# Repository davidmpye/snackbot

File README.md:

**Snackbot** is Makerspace's vending machine. It started life as a Polyvend
machine with a dead original controller (or at least it died while being experimented with...)
it's now a hybrid of a Raspberry Pi (running the user interface) and two RP2040 Pi Pico boards (driving the
hardware), all written in Rust.

This repository contains everything needed to reproduce the conversion:
firmware, PCB designs, the Pi-side application, and the 3D-printed / laser-cut
fixings.

Of note, it supports an MDB credit card reader, allowing contactless card payments

> 📷 *Photos to follow.*

---

## Architecture

```
                 ┌──────────────────────────────────────────┐
                 │ Raspberry Pi + Hyperpixel 480x800 display │
                 │          vmc-host (GTK4 app)              │
                 └───────────┬──────────────────┬───────────┘
                     USB HID │ + postcard-rpc   │ USB postcard-rpc
                             │                  │
            ┌────────────────┴───┐      ┌───────┴────────────────────────┐
            │  matrix-keyboard   │      │       vmc (RP2040 + PCB)        │
            │  (RP2040 + PCB)    │      │                                 │
            │                    │      │  • dispenser motor matrix       │
            │  • 3x8 keypad →    │      │  • MDB bus: coin acceptor &     │
            │    USB keyboard    │      │    cashless (card) reader       │
            │  • optional I2C    │      │  • chiller control + thermistor │
            │    text LCD        │      │  • hardware watchdog            │
            └────────────────────┘      └─────────────────────────────────┘
```

1. The customer types a selection on the machine's original membrane keypad
   (e.g. `A` then `4`). The **matrix-keyboard** Pico presents this to the Pi as
   an ordinary USB keyboard.
2. **vmc-host** shows the item, picture and price on the display and asks for
   confirmation (✔ / ✖).
3. On confirmation the host sends a `Vend` command to the **vmc** Pico, which
   collects payment over MDB (coins or contactless), drives the appropriate
   spiral/can motor, checks for a successful drop, and reports back.
4. The host shows success/failure and returns to idle.

The two Picos talk to the Pi using [postcard-rpc](https://github.com/jamesmunns/postcard-rpc)
over USB. The wire protocols are defined in small shared `*-icd` crates so the
host and firmware can never disagree about message formats.

---

## Repository layout

| Path | What it is |
|------|------------|
| [`vmc/fw`](vmc/fw) | **Vending Machine Controller firmware** – `no_std` Rust on RP2040 using [Embassy](https://embassy.dev). Drives motors, MDB peripherals, chiller and watchdog; exposes a postcard-rpc server over USB. |
| [`vmc/vmc-icd`](vmc/vmc-icd) | Interface Control Document crate for the VMC – shared request/response types and endpoint definitions. |
| [`vmc/pcb`](vmc/pcb) | KiCad project for the VMC board (power, level shifters, MDB interface, motor driver). Gerber job file included. |
| [`matrix-keyboard/fw`](matrix-keyboard/fw) | Firmware for the keypad board – USB HID keyboard + postcard-rpc endpoints for an optional I2C LCD. |
| [`matrix-keyboard/keyboard-icd`](matrix-keyboard/keyboard-icd) | ICD crate for the keypad board. |
| [`matrix-keyboard/pcb`](matrix-keyboard/pcb) | KiCad project for the keypad interface board (includes 3V3→5V level shifting for 5V LCDs). |
| [`vmc-host`](vmc-host) | The GTK4 application that runs on the Raspberry Pi – UI, state machine, stock list, and USB clients for both Picos. |
| [`fixings`](fixings) | OpenSCAD sources for the display mount, retaining tabs, LCD frame and laser-cut acrylic windows. See [`fixings/README.md`](fixings/README.md). |

---

## Components in detail

### `vmc` – Vending Machine Controller

The VMC firmware runs a set of Embassy tasks:

- **Motor driver** – drives the dispenser motor matrix via an 8-bit data bus
  plus three clock lines, OE and CLR (GPIO 0–12). Detects home position,
  stuck motors, and "one or no cans left" on the can vendor.
- **MDB (Multi-Drop Bus)** – the 9-bit serial bus used by vending peripherals,
  implemented with a PIO-backed 9-bit UART on GPIO 20/21. Two poll tasks handle
  the **coin acceptor** and a **cashless (card) device**.
- **Chiller** – reads a thermistor on ADC0 (GPIO 26) and publishes
  `ChillerStatus` to the host.
- **Watchdog** – hardware watchdog with a heartbeat LED on GPIO 22.
- **USB** – enumerates as a composite device, manufacturer `Snackbot`,
  product `vmc` (VID `0xDEAD`, PID `0xBEEF`).

The postcard-rpc API (from `vmc-icd`):

| Endpoint | Request | Response | Purpose |
|----------|---------|----------|---------|
| `/vmc/itemavailable` | `VendCommand` | `VendResult` | Check an item can be vended |
| `/vmc/vend` | `VendCommand` | `VendResult` | Take payment, then dispense |
| `/vmc/forcedispense` | `VendCommand` | `VendResult` | Dispense **without charging** (maintenance) |
| `/vmc/cancelvend` | `()` | `VendResult` | Cancel an in-progress vend *(not yet implemented)* |
| `/vmc/collectpayment` | `VendCommand` | `VendResult` | Charge without dispensing – lets people pay for e.g. filament |

| Topic (device → host) | Payload |
|-----------------------|---------|
| `/vmc/vend_progress` | `AwaitingPayment` / `Dispensing` |
| `/vmc/status/chiller` | `ChillerStatus` |

`VendCommand` is `{ row: u8, col: u8, price: u16 }` with the price in unscaled
pence. Failures are reported as a `VendError` (`MotorNotPresent`,
`MotorNotHome`, `MotorStuckHome`, `MotorStuckNotHome`, `OneOrNoCansLeft`,
`NoDropDetected`, `InvalidAddress`, `Cancelled`, `PaymentFailed`, `CommsFault`).

### `matrix-keyboard` – keypad interface

A small PCB that plugs into the vending machine's original 3×8 matrix keypad
header. The firmware scans the matrix and appears to the Pi as a **USB HID
keyboard**, so no custom input driver is needed on the Pi side.

It also exposes postcard-rpc endpoints for an optional **I2C character LCD**
(useful as a cheap secondary display, or as the *only* display if you don't
fit the Hyperpixel):

| Endpoint | Request | Purpose |
|----------|---------|---------|
| `setText` | `[[u8; 32]; 2]` | Set two 32-character lines of text |
| `setBacklight` | `bool` | Backlight on/off |

Topic `serviceMode` (`bool`) is published to the host.

### `vmc-host` – the Pi application

A GTK4 app (`uk.org.makerspace.snackbot`) sized for a 480×800 portrait display
(Pimoroni Hyperpixel 4). It is a simple event-driven state machine:

```
Idle ─▶ AwaitingConfirmation ─▶ AwaitingPayment ─▶ Dispensing ─▶ VendSuccess
  ▲            │                      │                 │              │
  │            ✖ cancel               ✖ cancel          └──▶ VendFailed │
  └────────────┴──────────────────────┴───────────── timeout / 2s ─────┘
```

- Letters `A`–`H` select a row, digits `0`–`9` a column; `Return` is ✔ confirm,
  `Escape` is ✖ cancel.
- Returns to idle automatically after 30 s of inactivity.
- Each screen is a GTK widget in a `Stack` (`make_selection_box`,
  `confirm_item_box`, `make_payment_box`, `vend_in_progress_box`, etc.).
- The stock list (name, image, price, row/col) currently lives in
  [`vmc-host/src/stock_info.rs`](vmc-host/src/stock_info.rs); product images
  are in `vmc-host/src/images/`.
- `rpc_shim.rs` spawns a Tokio runtime hosting the postcard-rpc clients for the
  VMC and the LCD, bridged to the GLib main loop with `async-channel`.

### `fixings` – mechanical parts

OpenSCAD sources for:

- `hyperpixel_mount.scad` / `hyperpixel_retaining_tabs.scad` – 3D-printed
  bracket and tabs to hold the Pi + Hyperpixel behind the fascia.
- `hyperpixel_lcd_window.scad` – laser-cut 3 mm clear acrylic window.
- `i2c_lcd_frame.scad` / `i2c_lcd_window.scad` – frame and window for the
  optional I2C text display.

---

## Building

### Prerequisites

- Rust toolchain (the firmware crates pin their version via
  `rust-toolchain.toml`; `rustup` will pick it up automatically).
- For firmware: the `thumbv6m-none-eabi` target and
  [`probe-rs`](https://probe.rs) (or `elf2uf2-rs` if you'd rather flash over
  USB bootloader).
- For the host: GTK4 development libraries (`libgtk-4-dev` on
  Debian/Raspberry Pi OS) and `libudev`.

### Firmware (either Pico)

```bash
cd vmc/fw            # or matrix-keyboard/fw
cargo run --release  # flashes via probe-rs (see .cargo/config.toml)
```

To produce a UF2 instead, swap the runner in `.cargo/config.toml` for the
commented-out `elf2uf2-rs -d` line, hold BOOTSEL while plugging in the Pico,
and `cargo run --release` again.

Logging is via `defmt` over RTT; set `DEFMT_LOG=debug` for more chatter.

The VMC firmware depends on two companion crates by the same author:
[`mdb-async`](https://github.com/davidmpye/mdb-async) and
[`pio-9bit-uart-async`](https://github.com/davidmpye/pio-9bit-uart-async).

### Host application

```bash
cd vmc-host
cargo build --release
./target/release/vmc-host
```

The app opens USB devices by product string (`vmc` and `matrix-keyboard`), so
you'll want a udev rule granting your user access to them, e.g.:

```
# /etc/udev/rules.d/99-snackbot.rules
SUBSYSTEM=="usb", ATTR{idVendor}=="dead", ATTR{idProduct}=="beef", MODE="0666"
```

(adjust for the keyboard board's VID/PID as well), then
`sudo udevadm control --reload && sudo udevadm trigger`.

For a kiosk deployment, run it under a minimal Wayland/X session on boot with
the Hyperpixel in portrait orientation.

### Hardware

Open the `.kicad_pro` files in `vmc/pcb` and `matrix-keyboard/pcb` with
KiCad 8+. Render the `.scad` files in `fixings/` with OpenSCAD and export STL
(for printing) or DXF (for laser cutting).

---

## Status / TODO

- [ ] `CancelVend` endpoint on the VMC
- [ ] Move stock list out of `stock_info.rs` into a config file
- [ ] Hook up `ItemAvailable` / `CollectPaymentOnly` in the host UI
- [ ] Photos and wiring diagrams
- [ ] Chiller status display on the host

---

## License

GPL-3.0 – see [LICENSE](LICENSE).

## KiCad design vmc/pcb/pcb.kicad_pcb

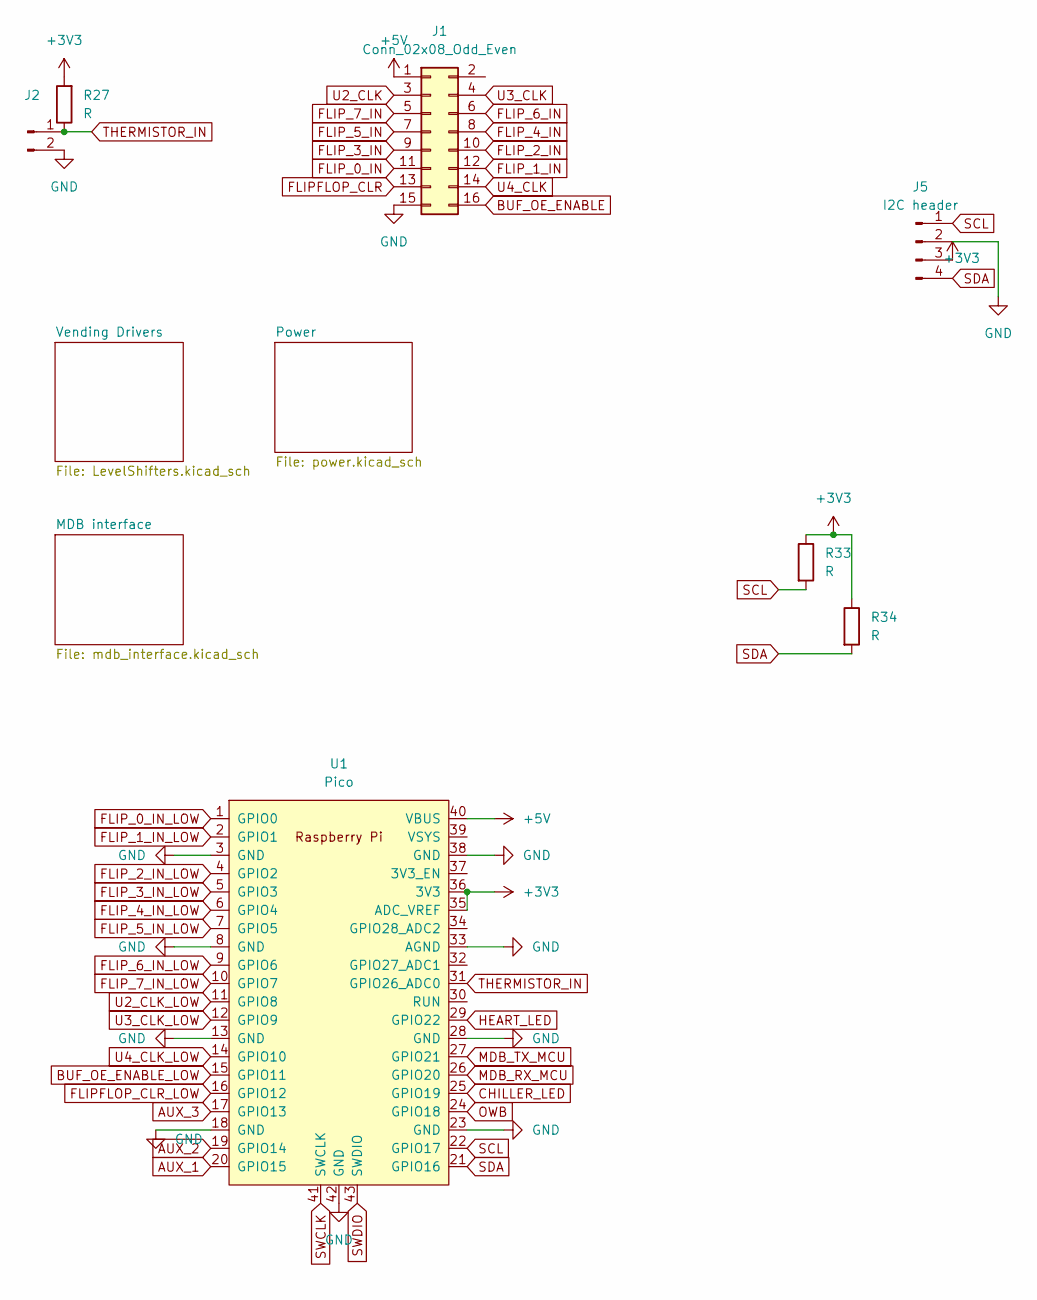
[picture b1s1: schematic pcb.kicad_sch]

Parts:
J1: Conn_02x08_Odd_Even; PinHeader_2x08_P2.54mm_Vertical
J2: Conn_01x02_Pin; JST_PH_B2B-PH-K_1x02_P2.00mm_Vertical
J5: I2C header; PinHeader_1x04_P2.54mm_Vertical
R27, R33, R34: R; R_1206_3216Metric
U1: Pico; RPi_Pico_SMD_TH

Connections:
+3V3: J5.3, R27.2, R33.1, R34.1, U1.35 (ADC_VREF), U1.36 (3V3); also elsewhere on the board
+5V: J1.1, U1.40 (VBUS); also elsewhere on the board
AUX_1: U1.20 (GPIO15); also elsewhere on the board
AUX_2: U1.19 (GPIO14); also elsewhere on the board
AUX_3: U1.17 (GPIO13); also elsewhere on the board
BUF_OE_ENABLE: J1.16; also elsewhere on the board
BUF_OE_ENABLE_LOW: U1.15 (GPIO11); also elsewhere on the board
CHILLER_LED: U1.25 (GPIO19); also elsewhere on the board
FLIPFLOP_CLR: J1.13; also elsewhere on the board
FLIPFLOP_CLR_LOW: U1.16 (GPIO12); also elsewhere on the board
FLIP_0_IN: J1.11; also elsewhere on the board
FLIP_0_IN_LOW: U1.1 (GPIO0); also elsewhere on the board
FLIP_1_IN: J1.12; also elsewhere on the board
FLIP_1_IN_LOW: U1.2 (GPIO1); also elsewhere on the board
FLIP_2_IN: J1.10; also elsewhere on the board
FLIP_2_IN_LOW: U1.4 (GPIO2); also elsewhere on the board
FLIP_3_IN: J1.9; also elsewhere on the board
FLIP_3_IN_LOW: U1.5 (GPIO3); also elsewhere on the board
FLIP_4_IN: J1.8; also elsewhere on the board
FLIP_4_IN_LOW: U1.6 (GPIO4); also elsewhere on the board
FLIP_5_IN: J1.7; also elsewhere on the board
FLIP_5_IN_LOW: U1.7 (GPIO5); also elsewhere on the board
FLIP_6_IN: J1.6; also elsewhere on the board
FLIP_6_IN_LOW: U1.9 (GPIO6); also elsewhere on the board
FLIP_7_IN: J1.5; also elsewhere on the board
FLIP_7_IN_LOW: U1.10 (GPIO7); also elsewhere on the board
GND: J1.15, J2.2, J5.2, U1.3 (GND), U1.8 (GND), U1.13 (GND), U1.18 (GND), U1.23 (GND), U1.28 (GND), U1.33 (AGND), U1.38 (GND), U1.42 (GND); also elsewhere on the board
HEART_LED: U1.29 (GPIO22); also elsewhere on the board
MDB_RX_MCU: U1.26 (GPIO20); also elsewhere on the board
MDB_TX_MCU: U1.27 (GPIO21); also elsewhere on the board
OWB: U1.24 (GPIO18); also elsewhere on the board
SCL: J5.1, R33.2, U1.22 (GPIO17)
SDA: J5.4, R34.2, U1.21 (GPIO16)
SWCLK: U1.41 (SWCLK); also elsewhere on the board
SWDIO: U1.43 (SWDIO); also elsewhere on the board
THERMISTOR_IN: J2.1, R27.1, U1.31 (GPIO26_ADC0)
U2_CLK: J1.3; also elsewhere on the board
U2_CLK_LOW: U1.11 (GPIO8); also elsewhere on the board
U3_CLK: J1.4; also elsewhere on the board
U3_CLK_LOW: U1.12 (GPIO9); also elsewhere on the board
U4_CLK: J1.14; also elsewhere on the board
U4_CLK_LOW: U1.14 (GPIO10); also elsewhere on the board

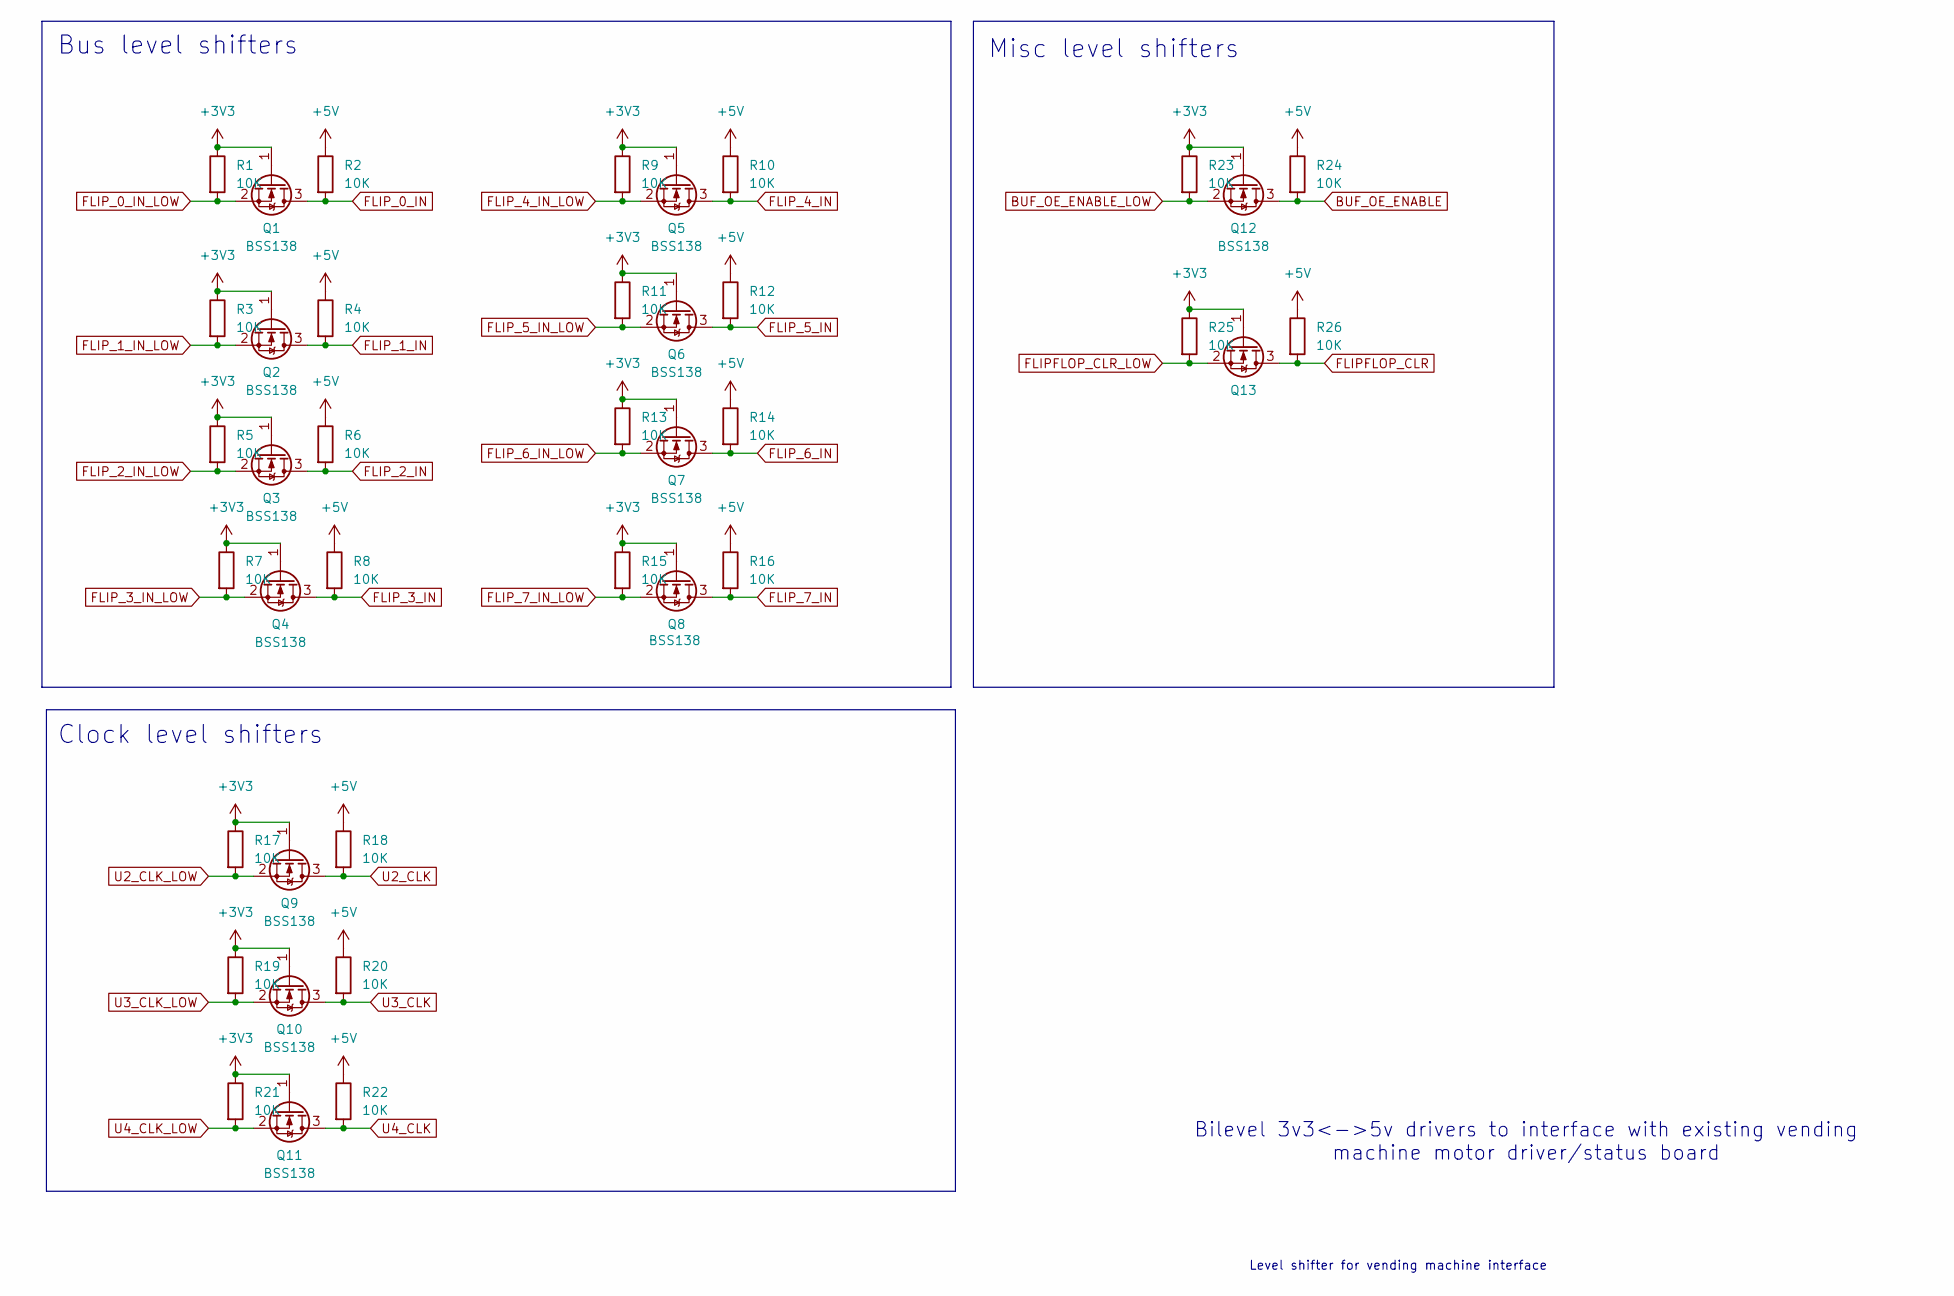
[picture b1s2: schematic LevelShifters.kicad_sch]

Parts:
Q1, Q2, Q3, Q4, Q5, Q6, Q7, Q8, Q9, Q10, Q11, Q12, Q13: BSS138; SOT-23
R1, R2, R3, R4, R5, R6, R7, R8, R9, R10, R11, R12, R13, R14, R15, R16, R17, R18, R19, R20, R21, R22, R23, R24, R25, R26: 10K; R_1206_3216Metric

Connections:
+3V3: Q1.1 (G), Q2.1 (G), Q3.1 (G), Q4.1 (G), Q5.1 (G), Q6.1 (G), Q7.1 (G), Q8.1 (G), Q9.1 (G), Q10.1 (G), Q11.1 (G), Q12.1 (G), Q13.1 (G), R1.1, R3.1, R5.1, R7.1, R9.1, R11.1, R13.1, R15.1, R17.1, R19.1, R21.1, R23.1, R25.1; also elsewhere on the board
+5V: R2.1, R4.1, R6.1, R8.1, R10.1, R12.1, R14.1, R16.1, R18.1, R20.1, R22.1, R24.1, R26.1; also elsewhere on the board
BUF_OE_ENABLE: Q12.3 (D), R24.2; also elsewhere on the board
BUF_OE_ENABLE_LOW: Q12.2 (S), R23.2; also elsewhere on the board
FLIPFLOP_CLR: Q13.3 (D), R26.2; also elsewhere on the board
FLIPFLOP_CLR_LOW: Q13.2 (S), R25.2; also elsewhere on the board
FLIP_0_IN: Q1.3 (D), R2.2; also elsewhere on the board
FLIP_0_IN_LOW: Q1.2 (S), R1.2; also elsewhere on the board
FLIP_1_IN: Q2.3 (D), R4.2; also elsewhere on the board
FLIP_1_IN_LOW: Q2.2 (S), R3.2; also elsewhere on the board
FLIP_2_IN: Q3.3 (D), R6.2; also elsewhere on the board
FLIP_2_IN_LOW: Q3.2 (S), R5.2; also elsewhere on the board
FLIP_3_IN: Q4.3 (D), R8.2; also elsewhere on the board
FLIP_3_IN_LOW: Q4.2 (S), R7.2; also elsewhere on the board
FLIP_4_IN: Q5.3 (D), R10.2; also elsewhere on the board
FLIP_4_IN_LOW: Q5.2 (S), R9.2; also elsewhere on the board
FLIP_5_IN: Q6.3 (D), R12.2; also elsewhere on the board
FLIP_5_IN_LOW: Q6.2 (S), R11.2; also elsewhere on the board
FLIP_6_IN: Q7.3 (D), R14.2; also elsewhere on the board
FLIP_6_IN_LOW: Q7.2 (S), R13.2; also elsewhere on the board
FLIP_7_IN: Q8.3 (D), R16.2; also elsewhere on the board
FLIP_7_IN_LOW: Q8.2 (S), R15.2; also elsewhere on the board
U2_CLK: Q9.3 (D), R18.2; also elsewhere on the board
U2_CLK_LOW: Q9.2 (S), R17.2; also elsewhere on the board
U3_CLK: Q10.3 (D), R20.2; also elsewhere on the board
U3_CLK_LOW: Q10.2 (S), R19.2; also elsewhere on the board
U4_CLK: Q11.3 (D), R22.2; also elsewhere on the board
U4_CLK_LOW: Q11.2 (S), R21.2; also elsewhere on the board

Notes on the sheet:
Bilevel 3v3<->5v drivers to interface with existing vending machine motor driver/status board
Level shifter for vending machine interface
Clock level shifters
Bus level shifters
Misc level shifters

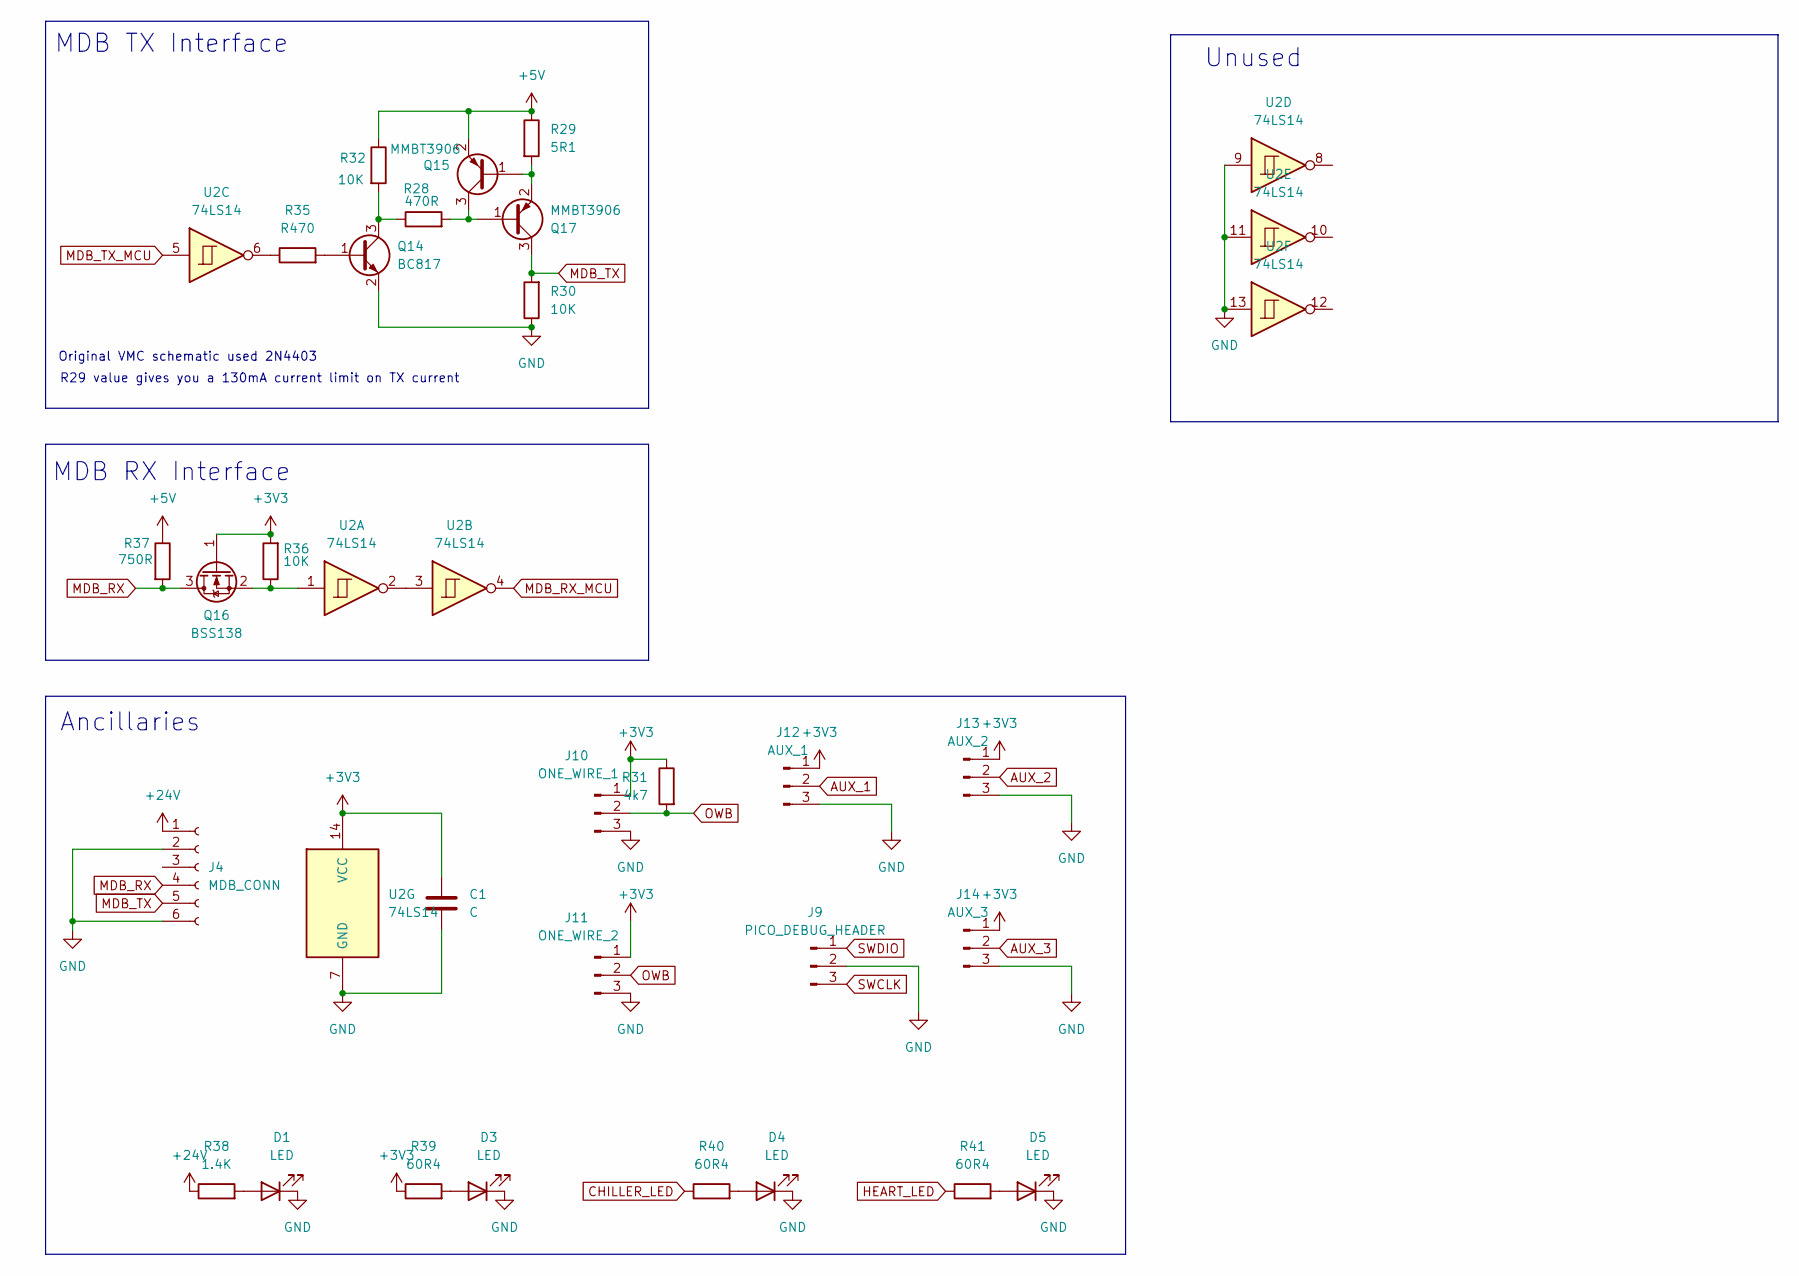
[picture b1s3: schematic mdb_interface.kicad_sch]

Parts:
C1: C; C_1206_3216Metric
D1, D3, D4, D5: LED; LED_1206_3216Metric_Pad1.42x1.75mm_HandSolder
J4: MDB_CONN; Molex_Mini-Fit_Jr_5566-06A_2x03_P4.20mm_Vertical
J9: PICO_DEBUG_HEADER; PinSocket_1x03_P2.54mm_Vertical
J10: ONE_WIRE_1; JST_PH_B3B-PH-K_1x03_P2.00mm_Vertical
J11: ONE_WIRE_2; JST_PH_B3B-PH-K_1x03_P2.00mm_Vertical
J12: AUX_1; JST_PH_B3B-PH-K_1x03_P2.00mm_Vertical
J13: AUX_2; JST_PH_B3B-PH-K_1x03_P2.00mm_Vertical
J14: AUX_3; JST_PH_B3B-PH-K_1x03_P2.00mm_Vertical
Q14: BC817; SOT-23
Q15, Q17: MMBT3906; SOT-23
Q16: BSS138; SOT-23
R28: 470R; R_1206_3216Metric
R29: 5R1; R_1206_3216Metric
R30, R32, R36: 10K; R_1206_3216Metric
R31: 4k7; R_1206_3216Metric
R35: R470; R_1206_3216Metric
R37: 750R; R_1206_3216Metric
R38: 1.4K; R_1206_3216Metric
R39, R40, R41: 60R4; R_1206_3216Metric
U2: 74LS14; SOIC-14_3.9x8.7mm_P1.27mm

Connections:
+3V3: C1.1, J10.1, J11.1, J12.1, J13.1, J14.1, Q16.1 (G), R31.1, R36.2, R39.1, U2.14 (VCC); also elsewhere on the board
+5V: Q15.2 (E), R29.1, R32.1, R37.1; also elsewhere on the board
+24V: J4.1, R38.1; also elsewhere on the board
AUX_1: J12.2; also elsewhere on the board
AUX_2: J13.2; also elsewhere on the board
AUX_3: J14.2; also elsewhere on the board
CHILLER_LED: R40.1; also elsewhere on the board
GND: C1.2, D1.1 (K), D3.1 (K), D4.1 (K), D5.1 (K), J4.2, J4.6, J9.2, J10.3, J11.3, J12.3, J13.3, J14.3, Q14.2 (E), R30.1, U2.7 (GND), U2.9, U2.11, U2.13; also elsewhere on the board
HEART_LED: R41.1; also elsewhere on the board
MDB_RX: J4.4, Q16.3 (D), R37.2
MDB_RX_MCU: U2.4; also elsewhere on the board
MDB_TX: J4.5, Q17.3 (C), R30.2
MDB_TX_MCU: U2.5; also elsewhere on the board
unnamed: D1.2 (A), R38.2
unnamed: D3.2 (A), R39.2
unnamed: D4.2 (A), R40.2
unnamed: D5.2 (A), R41.2
unnamed: Q14.1 (B), R35.2
unnamed: Q14.3 (C), R28.1, R32.2
unnamed: Q15.1 (B), Q17.2 (E), R29.2
unnamed: Q15.3 (C), Q17.1 (B), R28.2
unnamed: Q16.2 (S), R36.1, U2.1
unnamed: R35.1, U2.6
unnamed: U2.2, U2.3
OWB: J10.2, J11.2, R31.2; also elsewhere on the board
SWCLK: J9.3; also elsewhere on the board
SWDIO: J9.1; also elsewhere on the board

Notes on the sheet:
MDB RX Interface
MDB TX Interface
R29 value gives you a 130mA current limit on TX current
Ancillaries
Unused
Original VMC schematic used 2N4403

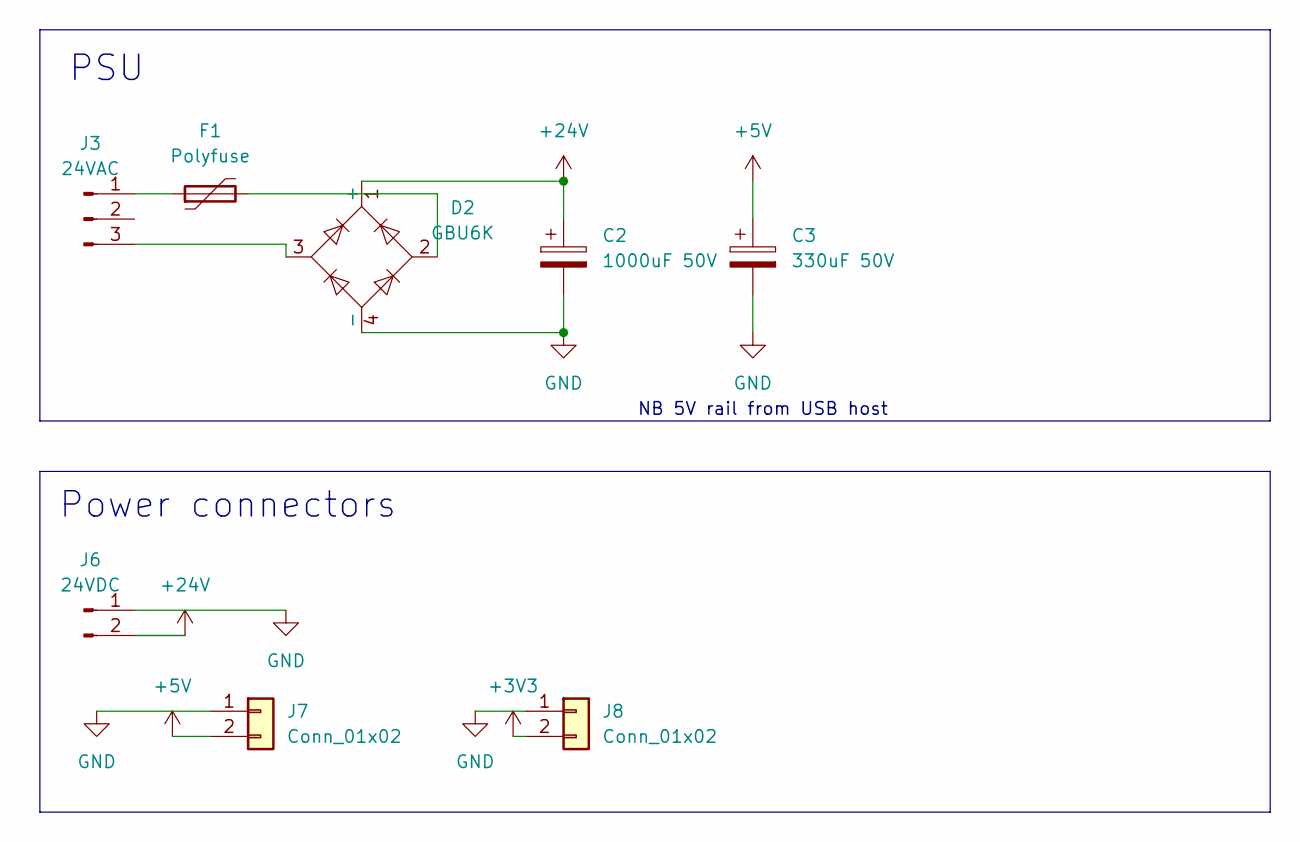
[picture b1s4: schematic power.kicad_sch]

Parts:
C2: 1000uF 50V; CP_Radial_D12.5mm_P5.00mm
C3: 330uF 50V; CP_Radial_D10.0mm_P5.00mm
D2: GBU6K; Diode_Bridge_Vishay_GBU
F1: Polyfuse; FUS_RKEF300_TYCO_TYC
J3: 24VAC; JST_VH_B3P-VH-B_1x03_P3.96mm_Vertical
J6: 24VDC; JST_VH_B2P-VH_1x02_P3.96mm_Vertical
J7, J8: Conn_01x02; PinHeader_1x02_P2.54mm_Vertical

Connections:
+3V3: J8.2; also elsewhere on the board
+5V: C3.1, J7.2; also elsewhere on the board
+24V: C2.1, D2.1 (+), J6.2; also elsewhere on the board
GND: C2.2, C3.2, D2.4 (-), J6.1, J7.1, J8.1; also elsewhere on the board
unnamed: D2.2, F1.2
unnamed: F1.1, J3.1
unnamed: D2.3, J3.3

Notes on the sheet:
PSU
NB 5V rail from USB host
Power connectors

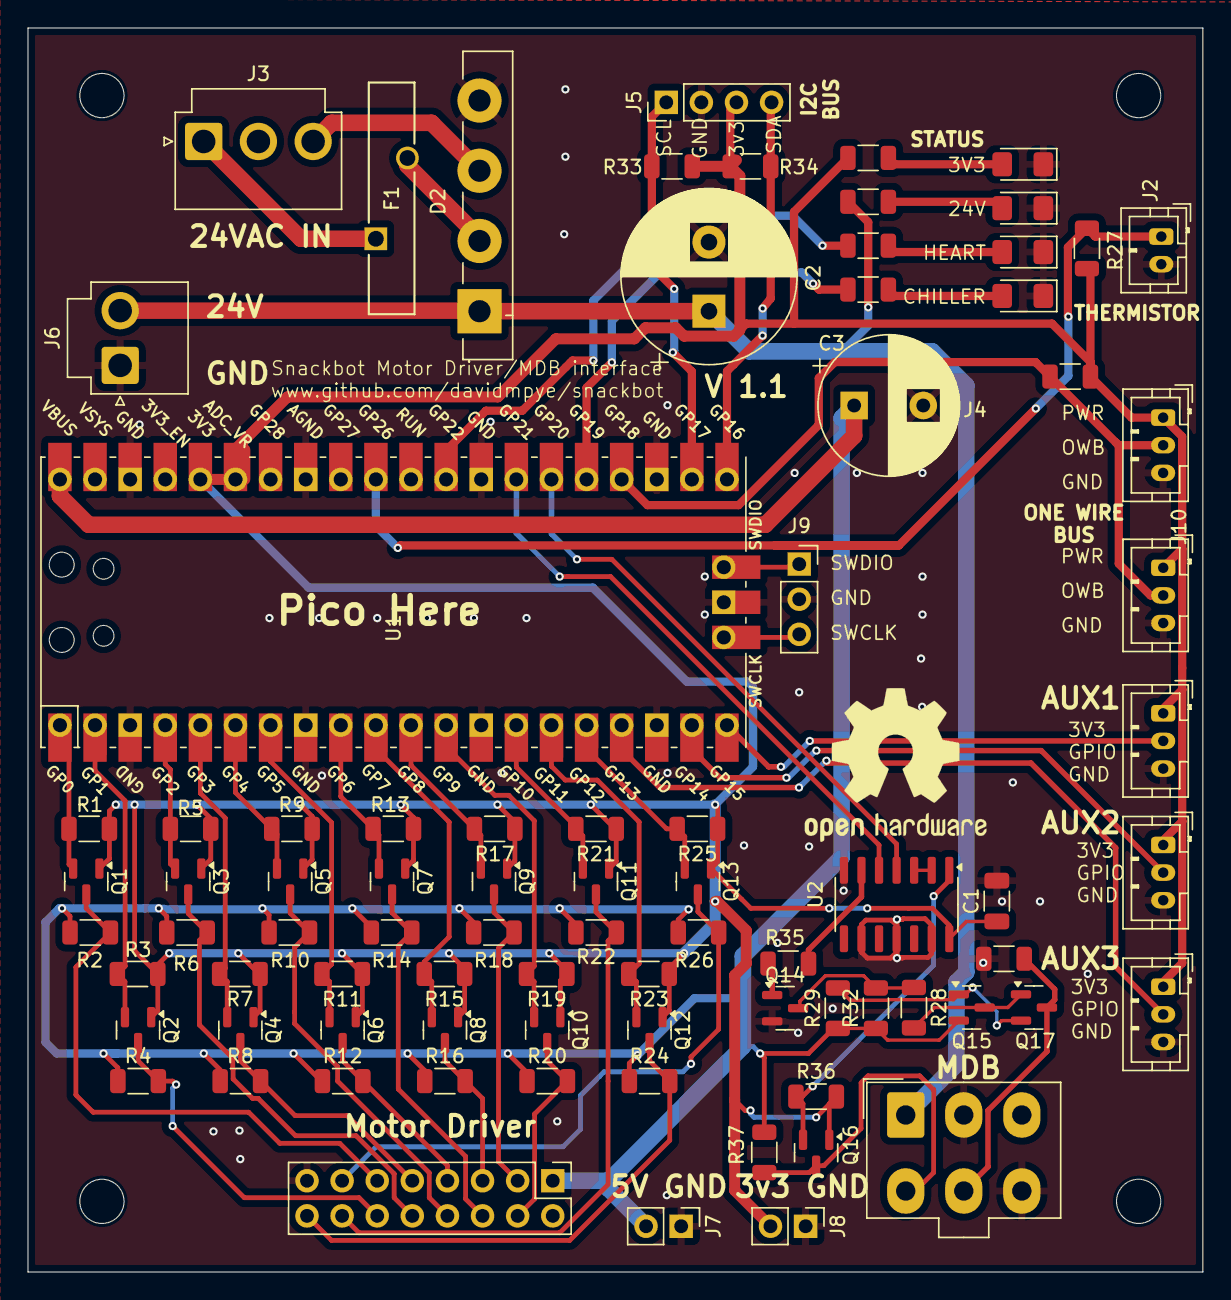
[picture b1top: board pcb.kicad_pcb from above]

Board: 2 copper layers, 85.0 x 90.0 mm, 83 parts (0 on the bottom side), 59 nets.

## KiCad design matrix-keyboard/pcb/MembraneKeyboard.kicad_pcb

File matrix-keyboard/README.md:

# Matrix-keyboard

Matrix-keyboard is a Pi Pico + small PCB designed to connect to the vending machine matrix keypad header and emulate a USB keyboard for feeding these input events to the Pi.

## Description
The vending machine keypad interface is a 3 x 8 matrix of key buttons.
This firmware appears as a USB HID Keyboard and the matrix keypad button presses are shared to the USB host as keyboard button keypresses.

The firmware also provides postcard-rpc endpoints (see keyboard-icd subfolder) to allow the Host to set the text and control the backlight of an optionally attached I2C LCD (the schematic includes 3v3->5v level shifting to ensure reliable operation with 5V-driven LCDs

![Matrix keyboard picture](https://private-user-images.githubusercontent.com/2261985/400223531-3191ab20-acc9-444a-97f4-25ef8820f795.jpg?jwt=eyJhbGciOiJIUzI1NiIsInR5cCI6IkpXVCJ9.eyJpc3MiOiJnaXRodWIuY29tIiwiYXVkIjoicmF3LmdpdGh1YnVzZXJjb250ZW50LmNvbSIsImtleSI6ImtleTUiLCJleHAiOjE3MzYxMDA0MzYsIm5iZiI6MTczNjEwMDEzNiwicGF0aCI6Ii8yMjYxOTg1LzQwMDIyMzUzMS0zMTkxYWIyMC1hY2M5LTQ0NGEtOTdmNC0yNWVmODgyMGY3OTUuanBnP1gtQW16LUFsZ29yaXRobT1BV1M0LUhNQUMtU0hBMjU2JlgtQW16LUNyZWRlbnRpYWw9QUtJQVZDT0RZTFNBNTNQUUs0WkElMkYyMDI1MDEwNSUyRnVzLWVhc3QtMSUyRnMzJTJGYXdzNF9yZXF1ZXN0JlgtQW16LURhdGU9MjAyNTAxMDVUMTgwMjE2WiZYLUFtei1FeHBpcmVzPTMwMCZYLUFtei1TaWduYXR1cmU9Yzg4ZTJkZDhmNmI2NzI0YzIyZTFjOTJjZjUzNzYxODY0MGI2NDdlNWEwMTFjMmZhMjk5MTRlNDcxYzIzOWU1ZSZYLUFtei1TaWduZWRIZWFkZXJzPWhvc3QifQ.oYjQgVpXzc-qRg_nyyYltGReJC5QKtszokIlRf1qOLs)

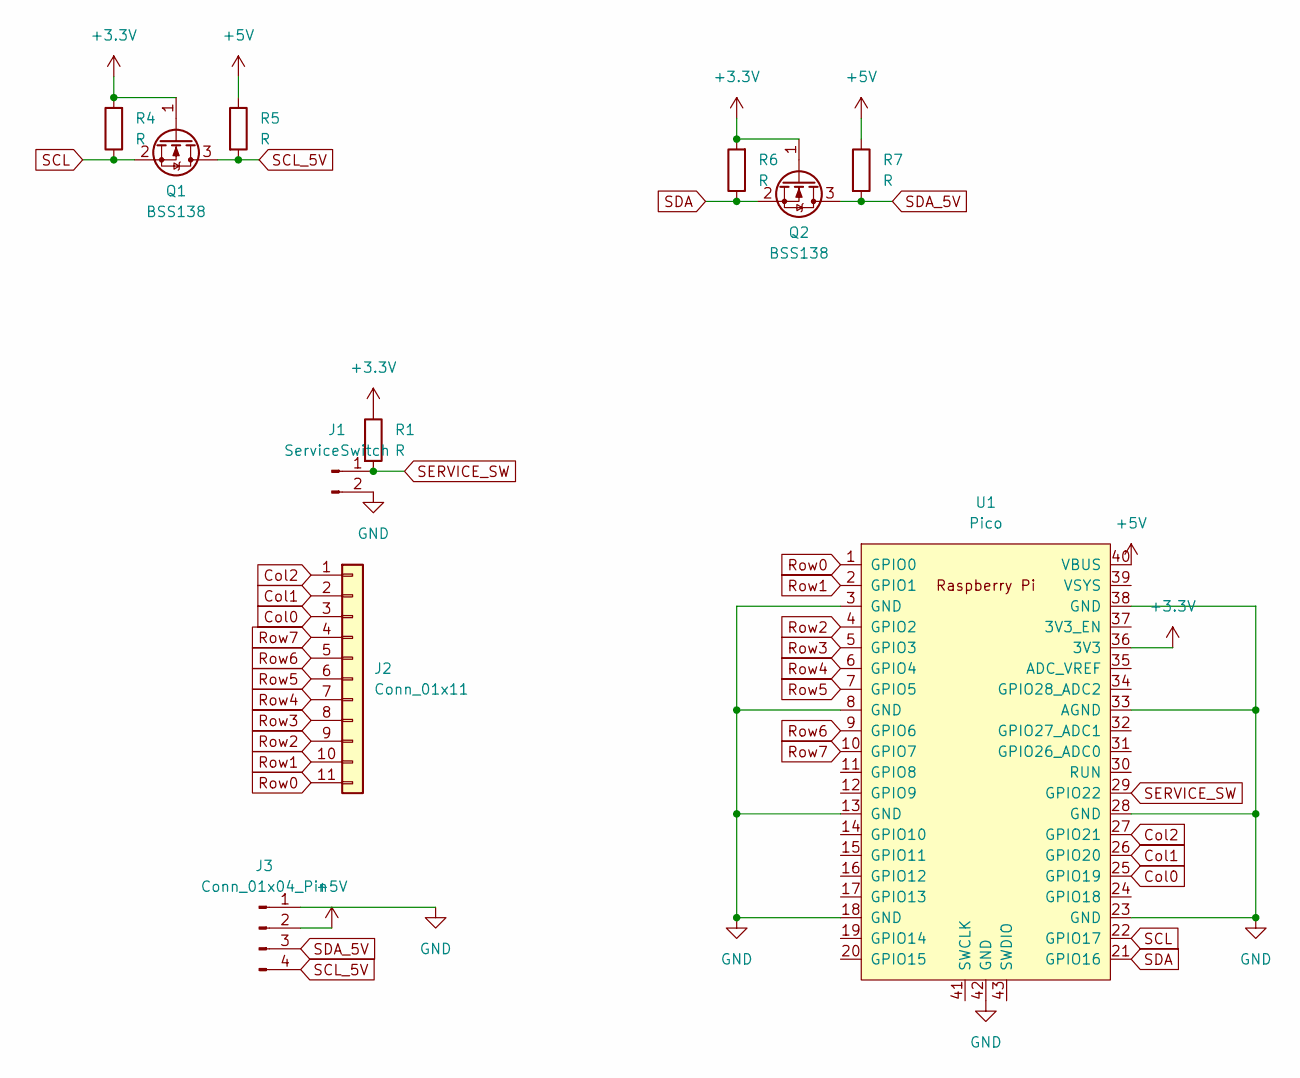
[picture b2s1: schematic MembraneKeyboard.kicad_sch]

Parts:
J1: ServiceSwitch; PinHeader_1x02_P2.54mm_Vertical
J2: Conn_01x11; PinHeader_1x11_P2.54mm_Vertical
J3: Conn_01x04_Pin; PinHeader_1x04_P2.54mm_Vertical
Q1, Q2: BSS138; SOT-23
R1, R4, R5, R6, R7: R; R_1206_3216Metric
U1: Pico; RPi_Pico_SMD_TH

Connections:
+3.3V: Q1.1 (G), Q2.1 (G), R1.1, R4.2, R6.2, U1.36 (3V3)
+5V: J3.2, R5.1, R7.1, U1.40 (VBUS)
Col0: J2.3, U1.25 (GPIO19)
Col1: J2.2, U1.26 (GPIO20)
Col2: J2.1, U1.27 (GPIO21)
GND: J1.2, J3.1, U1.3 (GND), U1.8 (GND), U1.13 (GND), U1.18 (GND), U1.23 (GND), U1.28 (GND), U1.33 (AGND), U1.38 (GND), U1.42 (GND)
Row0: J2.11, U1.1 (GPIO0)
Row1: J2.10, U1.2 (GPIO1)
Row2: J2.9, U1.4 (GPIO2)
Row3: J2.8, U1.5 (GPIO3)
Row4: J2.7, U1.6 (GPIO4)
Row5: J2.6, U1.7 (GPIO5)
Row6: J2.5, U1.9 (GPIO6)
Row7: J2.4, U1.10 (GPIO7)
SCL: Q1.2 (S), R4.1, U1.22 (GPIO17)
SCL_5V: J3.4, Q1.3 (D), R5.2
SDA: Q2.2 (S), R6.1, U1.21 (GPIO16)
SDA_5V: J3.3, Q2.3 (D), R7.2
SERVICE_SW: J1.1, R1.2, U1.29 (GPIO22)

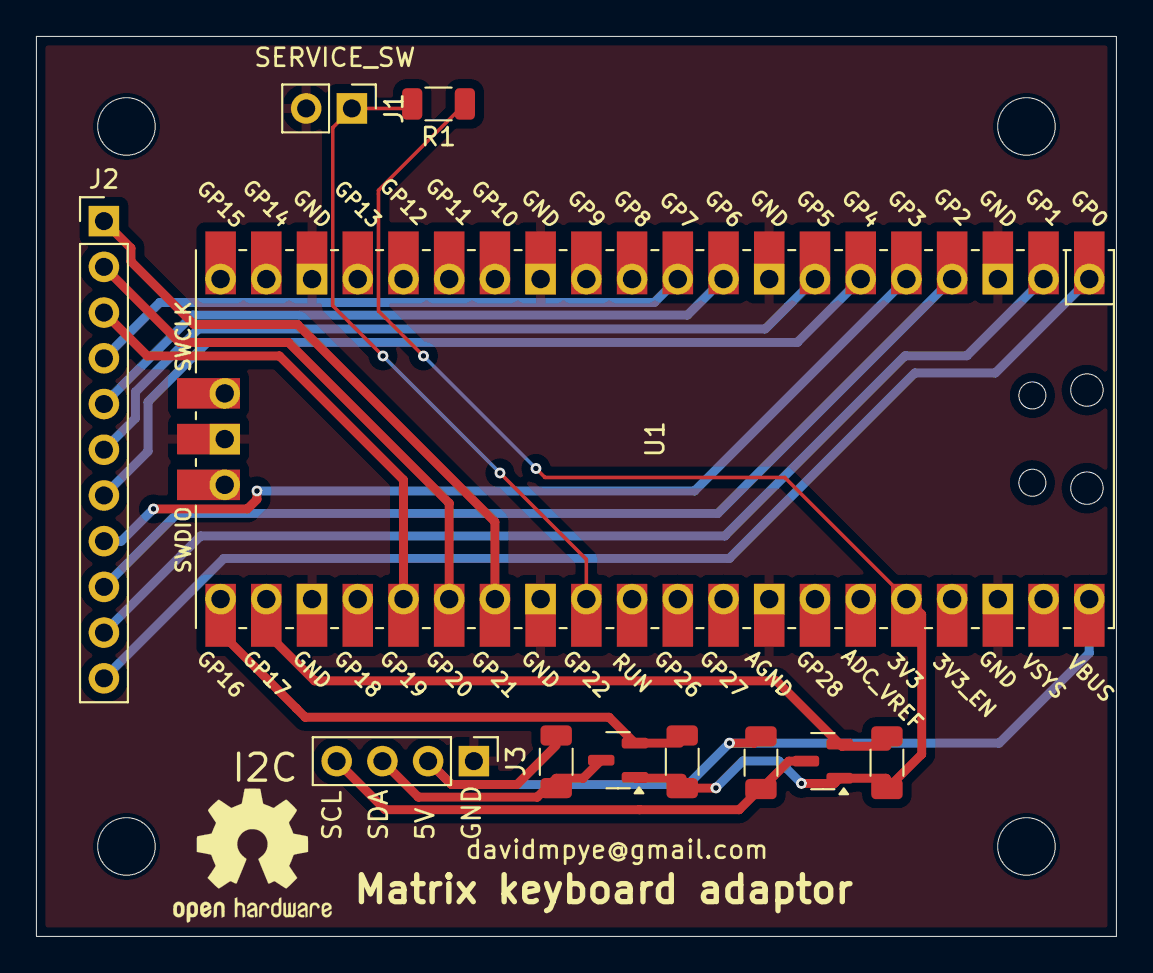
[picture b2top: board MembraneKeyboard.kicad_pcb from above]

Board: 2 copper layers, 60.0 x 50.0 mm, 11 parts (0 on the bottom side), 19 nets.
